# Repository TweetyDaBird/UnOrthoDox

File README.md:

|  |  | |
| --------------------------------------- | --------------------------------------- | --------------------------------------- |
| | |

# UnOrthoDox
A 'simple' and low cost hot-swap Numpad (available in 17-18 or 20 key versions) with support for dual encoders, and using a low cost but powerfull controller (RP2040-Zero). The design is dual sided, so flipping it over and building it as a 'SouthPaw' configuration is outright easy. A single plate/case design with cut-outs for all key configurations available in Black or White makes it easy to build a complete Numpad that fit's in well witha 60% keyboard in size and looks. The same plates/components fit both the 20-key PCB variant and the PCB-variant for a 17-18 key classic numpad layout. 

The name comes from the slightly unortodox placement of the controller straddling the hot-swap socket, with not all pins soldered, and the fact that it can be built as a 20-key ortholinear macro pad.

 - Full Sandwich Case design
 - Low cost/Simple to build
 - Powerful and Flexible MCU
 - Compatible with QMK/Vial and ZMK firmware
 - Reversible for SouthPaw's
 - Dual Rotary Encoders
 - Per-Key RGB
 - Build instructions are printed on the backplate for an easy build.

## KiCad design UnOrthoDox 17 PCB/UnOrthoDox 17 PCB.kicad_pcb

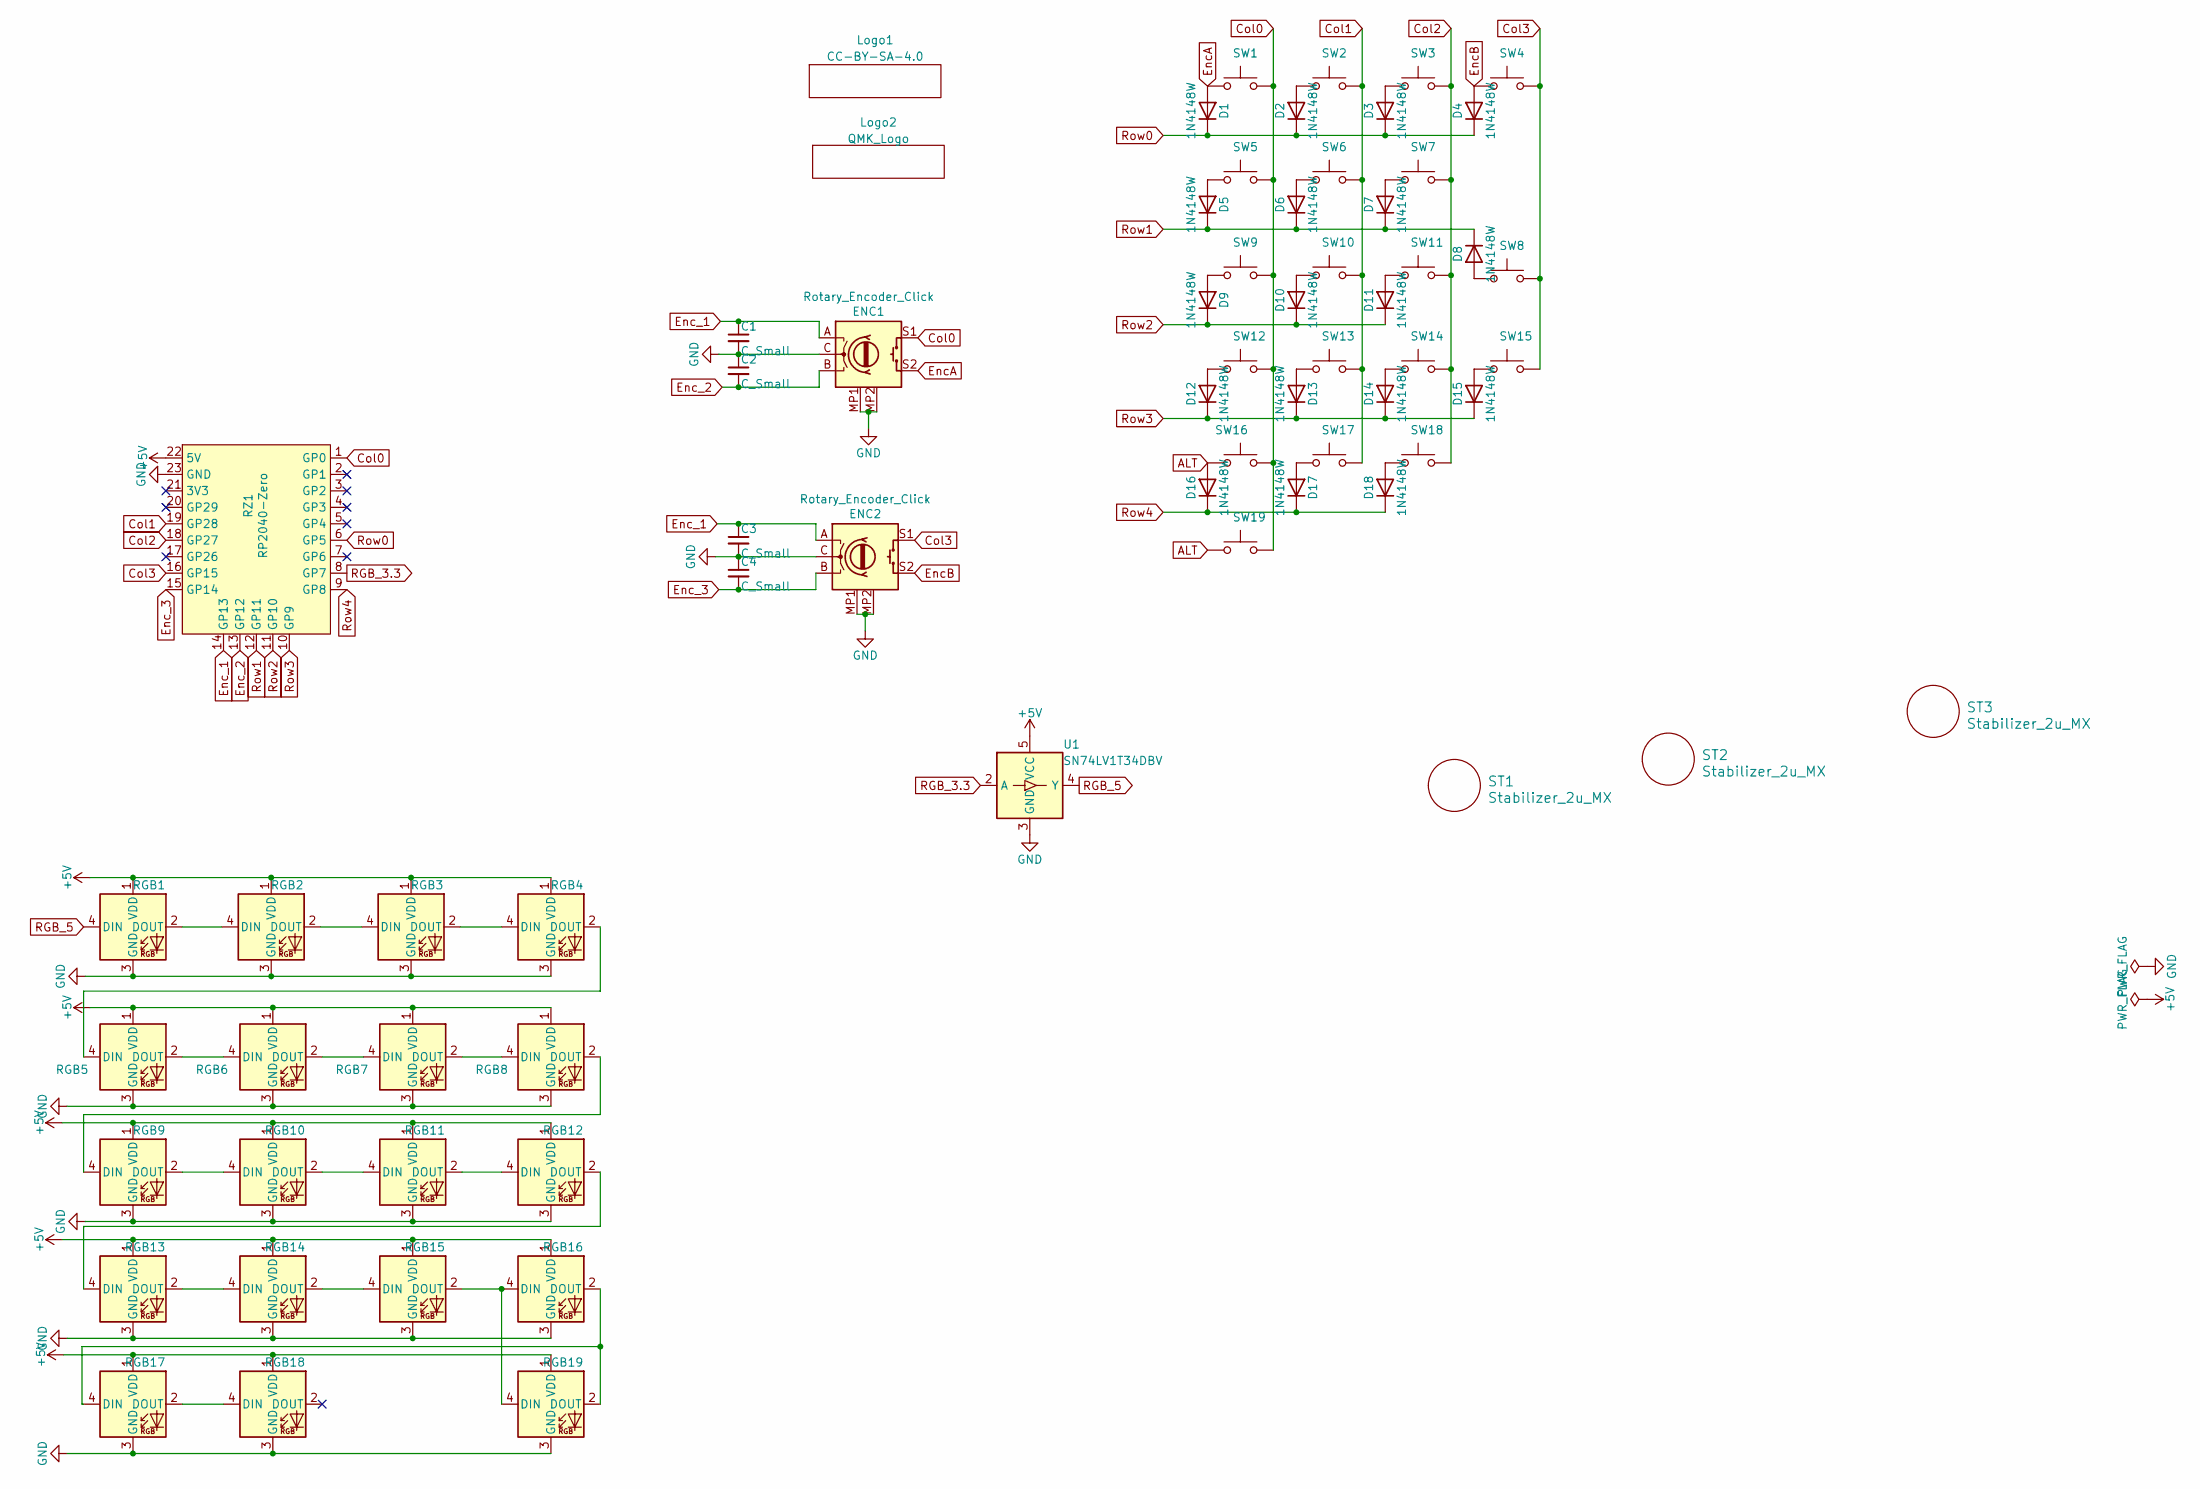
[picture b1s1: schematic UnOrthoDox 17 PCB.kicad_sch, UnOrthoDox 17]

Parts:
C1, C2, C3, C4: C_Small; C_0603_1608Metric_Pad1.08x0.95mm_HandSolder
D1, D2, D3, D4, D5, D6, D7, D8, D9, D10, D11, D12, D13, D14, D15, D16, D17, D18: 1N4148W; D_SOD-123
ENC1, ENC2: Rotary_Encoder_Click; Encoder_Alps_EC11E_Small
Logo1: CC-BY-SA-4.0; CC_BY_SA_40_line
Logo2: QMK_Logo; Powered_by_QMK
RGB1, RGB2, RGB3, RGB4, RGB5, RGB6, RGB7, RGB8, RGB9, RGB10, RGB11, RGB12, RGB13, RGB14, RGB15, RGB16, RGB17, RGB18, RGB19: SK6812MINI-E; MX_SK6812MINI-E_REVERSIBLE
RZ1: RP2040-Zero; RP2040-Zero_reverse_mount_flipped
ST1, ST2, ST3: Stabilizer_2u_MX; Stabilizer_Cherry_MX_2.00u
SW1, SW2, SW3, SW4, SW5, SW6, SW7, SW8, SW9, SW10, SW11, SW12, SW13, SW14, SW15, SW16, SW17, SW18, SW19: SW_MX_HotSwap; SW_MX_HotSwap_Reversible
U1: SN74LV1T34DBV; SOT-23-5

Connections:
+5V: RGB1.1 (VDD), RGB2.1 (VDD), RGB3.1 (VDD), RGB4.1 (VDD), RGB5.1 (VDD), RGB6.1 (VDD), RGB7.1 (VDD), RGB8.1 (VDD), RGB9.1 (VDD), RGB10.1 (VDD), RGB11.1 (VDD), RGB12.1 (VDD), RGB13.1 (VDD), RGB14.1 (VDD), RGB15.1 (VDD), RGB16.1 (VDD), RGB17.1 (VDD), RGB18.1 (VDD), RGB19.1 (VDD), RZ1.22 (5V), U1.5 (VCC)
ALT: D16.2 (A), SW16.2, SW19.1
Col0: ENC1.S1, RZ1.1 (GP0), SW1.2, SW5.2, SW9.2, SW12.2, SW16.1, SW19.2
Col1: RZ1.19 (GP28), SW2.2, SW6.2, SW10.2, SW13.2, SW17.2
Col2: RZ1.18 (GP27), SW3.2, SW7.2, SW11.2, SW14.2, SW18.2
Col3: ENC2.S1, RZ1.16 (GP15), SW4.2, SW8.2, SW15.2
EncA: D1.2 (A), ENC1.S2, SW1.1
EncB: D4.2 (A), ENC2.S2, SW4.1
Enc_1: C1.1, C3.1, ENC1.A, ENC2.A, RZ1.14 (GP13)
Enc_2: C2.2, ENC1.B, RZ1.13 (GP12)
Enc_3: C4.2, ENC2.B, RZ1.15 (GP14)
GND: C1.2, C2.1, C3.2, C4.1, ENC1.C, ENC1.MP1 (GND), ENC1.MP2 (GND), ENC2.C, ENC2.MP1 (GND), ENC2.MP2 (GND), RGB1.3 (GND), RGB2.3 (GND), RGB3.3 (GND), RGB4.3 (GND), RGB5.3 (GND), RGB6.3 (GND), RGB7.3 (GND), RGB8.3 (GND), RGB9.3 (GND), RGB10.3 (GND), RGB11.3 (GND), RGB12.3 (GND), RGB13.3 (GND), RGB14.3 (GND), RGB15.3 (GND), RGB16.3 (GND), RGB17.3 (GND), RGB18.3 (GND), RGB19.3 (GND), RZ1.23 (GND), U1.3 (GND)
unnamed: D2.2 (A), SW2.1
unnamed: D3.2 (A), SW3.1
unnamed: D5.2 (A), SW5.1
unnamed: D6.2 (A), SW6.1
unnamed: D7.2 (A), SW7.1
unnamed: D8.2 (A), SW8.1
unnamed: D9.2 (A), SW9.1
unnamed: D10.2 (A), SW10.1
unnamed: D11.2 (A), SW11.1
unnamed: D12.2 (A), SW12.1
unnamed: D13.2 (A), SW13.1
unnamed: D14.2 (A), SW14.1
unnamed: D15.2 (A), SW15.1
unnamed: D17.2 (A), SW17.1
unnamed: D18.2 (A), SW18.1
unnamed: RGB1.2 (DOUT), RGB2.4 (DIN)
unnamed: RGB2.2 (DOUT), RGB3.4 (DIN)
unnamed: RGB3.2 (DOUT), RGB4.4 (DIN)
unnamed: RGB4.2 (DOUT), RGB5.4 (DIN)
unnamed: RGB5.2 (DOUT), RGB6.4 (DIN)
unnamed: RGB6.2 (DOUT), RGB7.4 (DIN)
unnamed: RGB7.2 (DOUT), RGB8.4 (DIN)
unnamed: RGB8.2 (DOUT), RGB9.4 (DIN)
unnamed: RGB9.2 (DOUT), RGB10.4 (DIN)
unnamed: RGB10.2 (DOUT), RGB11.4 (DIN)
unnamed: RGB11.2 (DOUT), RGB12.4 (DIN)
unnamed: RGB12.2 (DOUT), RGB13.4 (DIN)
unnamed: RGB13.2 (DOUT), RGB14.4 (DIN)
unnamed: RGB14.2 (DOUT), RGB15.4 (DIN)
unnamed: RGB15.2 (DOUT), RGB16.4 (DIN), RGB19.4 (DIN)
unnamed: RGB16.2 (DOUT), RGB17.4 (DIN), RGB19.2 (DOUT)
unnamed: RGB17.2 (DOUT), RGB18.4 (DIN)
RGB_3.3: RZ1.8 (GP7), U1.2 (A)
RGB_5: RGB1.4 (DIN), U1.4 (Y)
Row0: D1.1 (K), D2.1 (K), D3.1 (K), D4.1 (K), RZ1.6 (GP5)
Row1: D5.1 (K), D6.1 (K), D7.1 (K), D8.1 (K), RZ1.12 (GP11)
Row2: D9.1 (K), D10.1 (K), D11.1 (K), RZ1.11 (GP10)
Row3: D12.1 (K), D13.1 (K), D14.1 (K), D15.1 (K), RZ1.10 (GP9)
Row4: D16.1 (K), D17.1 (K), D18.1 (K), RZ1.9 (GP8)

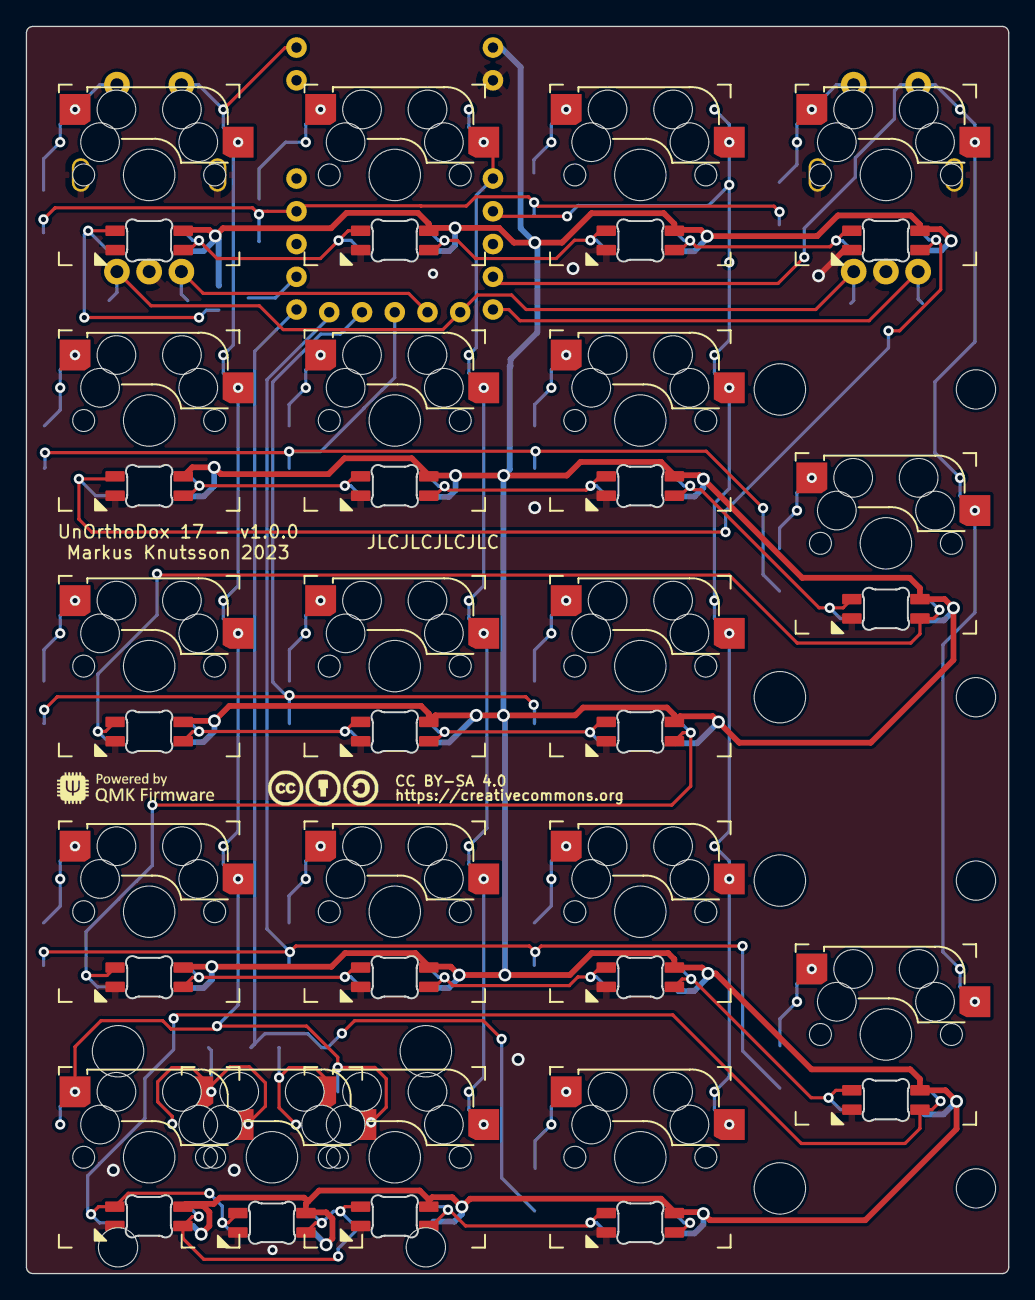
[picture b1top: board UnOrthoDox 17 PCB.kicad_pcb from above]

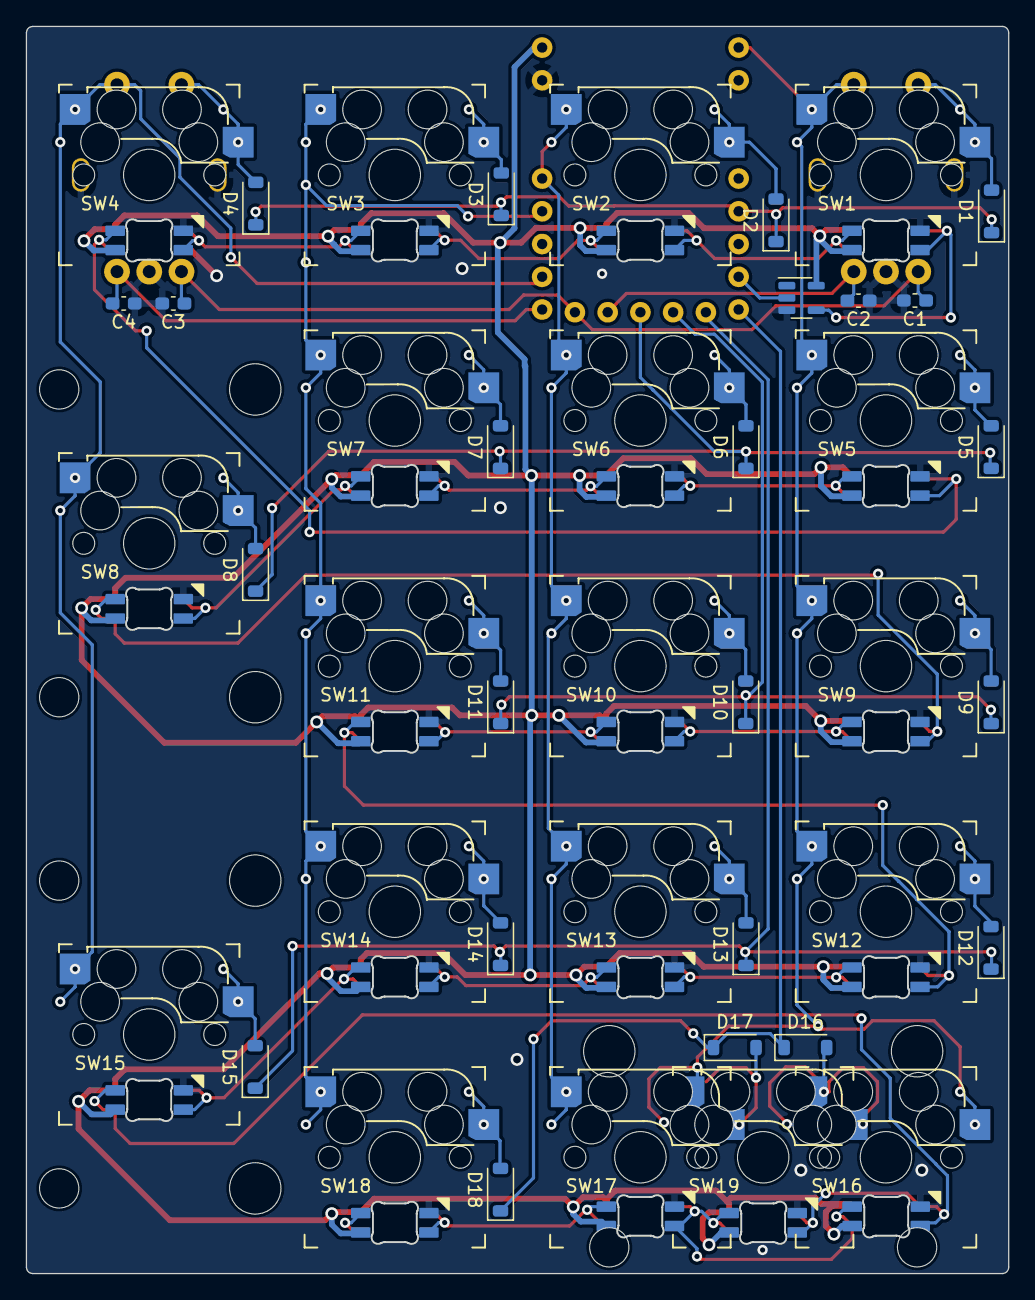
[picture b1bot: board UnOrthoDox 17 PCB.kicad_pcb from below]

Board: 2 copper layers, 76.1 x 96.7 mm, 69 parts (24 on the bottom side), 51 nets.

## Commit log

2023-04-23 First version
2023-07-10 Added 17
2023-07-11 Final tweaks 17/20 PCB
2023-07-11 Reworked plates for release
2023-07-11 Updated renders
2023-07-11 Fixed filename
2023-07-11 Update README.md
    Added renders to readme

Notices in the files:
UnOrthoDox 17 PCB/UnOrthoDox 17 PCB.kicad_pcb:
Licensed under Creative Commons BY-SA 4.0 International
